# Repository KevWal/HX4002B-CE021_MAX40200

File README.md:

# HX4002B-CE021_MAX40200
PCB for a HX4002B 3.3v boost converter and 3 x MAX40200 ideal diodes.  

Ordered from https://JLCPCB.com/, looks and works great.

Allows this setup:
https://www.qsl.net/zl1rs/balloon6.html

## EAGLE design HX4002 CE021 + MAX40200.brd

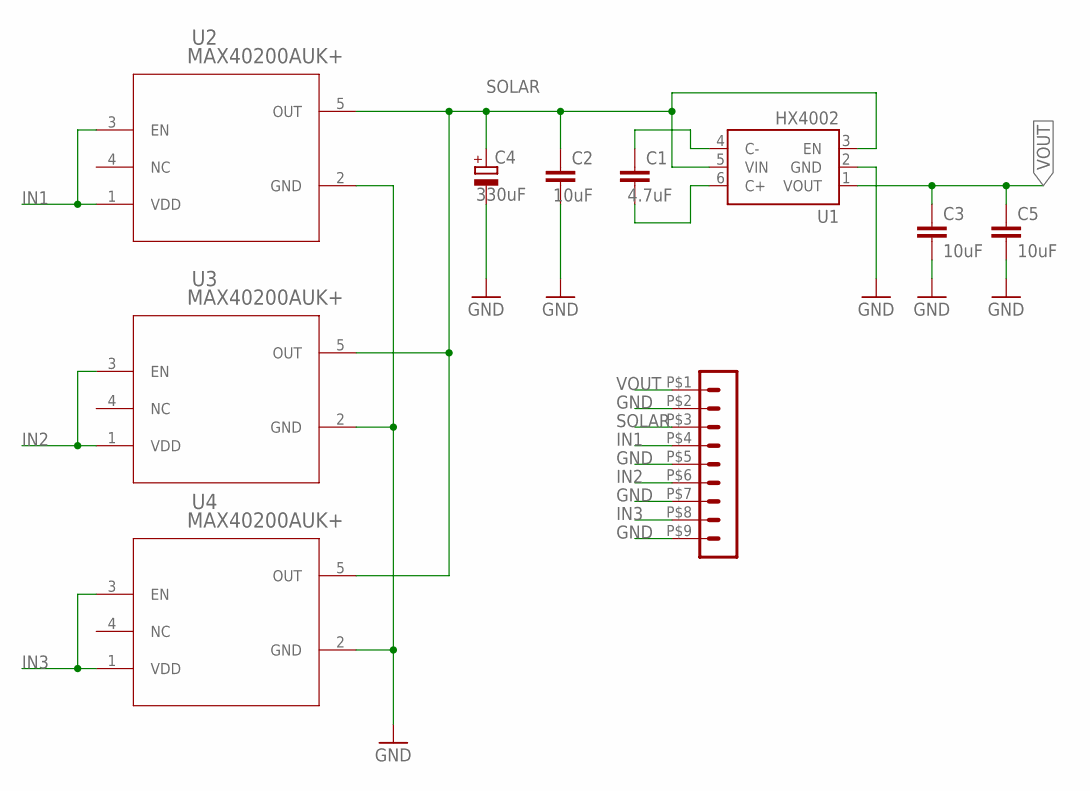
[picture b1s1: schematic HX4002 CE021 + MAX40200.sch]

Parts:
C1: 4.7uF; 0805
C2, C3, C5: 10uF; 0805
C4: 330uF; SMC_C
U1: HX4002; SOT23-6
U2, U3, U4: MAX40200AUK+; 21-0057F_MXM
X2: M_1R09_50MIL-V

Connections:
GND: C2.2, C3.2, C4.-, C5.2, U1.2 (GND), U2.2 (GND), U3.2 (GND), U4.2 (GND), X2.P$2 (2), X2.P$5 (5), X2.P$7 (7), X2.P$9 (9)
IN1: U2.1 (VDD), U2.3 (EN), X2.P$4 (4)
IN2: U3.1 (VDD), U3.3 (EN), X2.P$6 (6)
IN3: U4.1 (VDD), U4.3 (EN), X2.P$8 (8)
unnamed: C1.1, U1.4 (C-)
unnamed: C1.2, U1.6 (C+)
SOLAR: C2.1, C4.+, U1.3 (EN), U1.5 (VIN), U2.5 (OUT), U3.5 (OUT), U4.5 (OUT), X2.P$3 (3)
VOUT: C3.1, C5.1, U1.1 (VOUT), X2.P$1 (1)

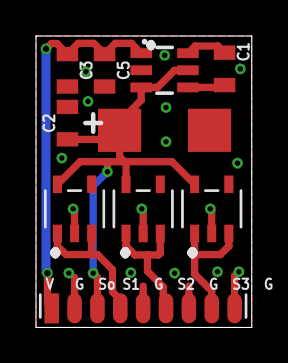
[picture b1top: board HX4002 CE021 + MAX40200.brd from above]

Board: 2 copper layers, 12.0 x 16.2 mm, 10 parts (0 on the bottom side), 8 nets.

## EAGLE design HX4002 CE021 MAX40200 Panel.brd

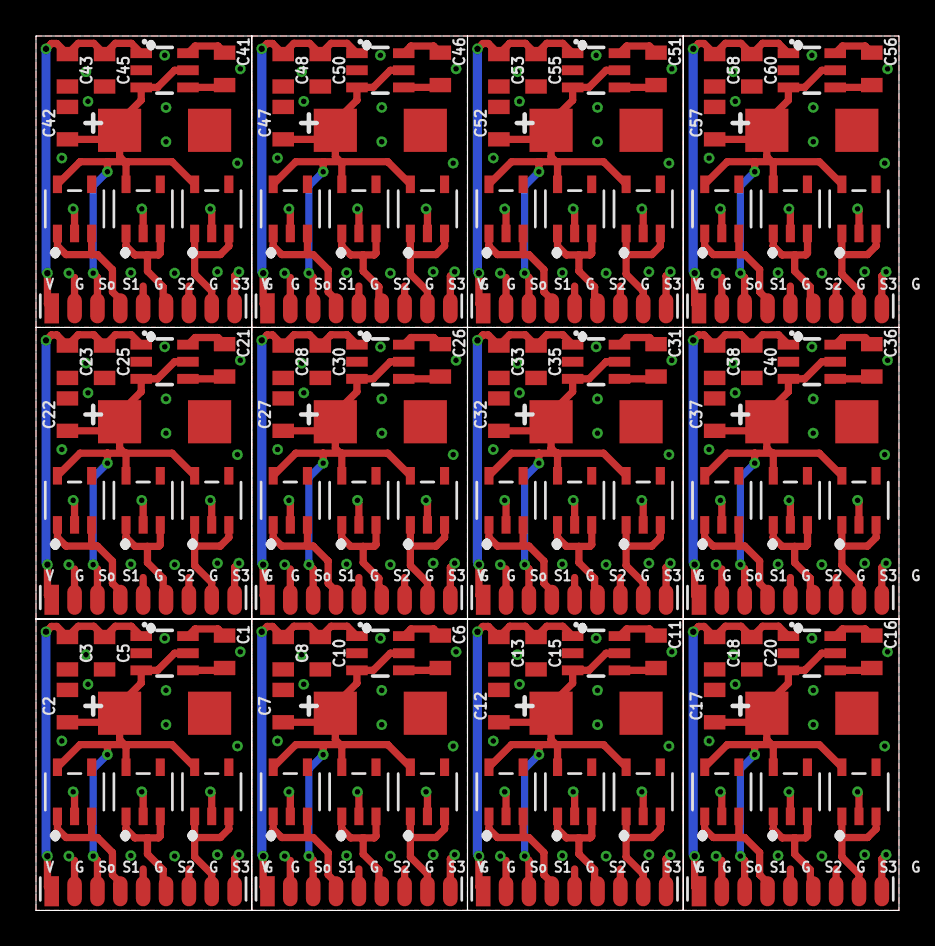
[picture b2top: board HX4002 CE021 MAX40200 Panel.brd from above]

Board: 2 copper layers, 47.9 x 48.6 mm, 120 parts (0 on the bottom side), 96 nets.

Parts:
C1, C6, C11, C16, C21, C26, C31, C36, C41, C46, C51, C56: 4.7uF; 0805
C2, C3, C5, C7, C8, C10, C12, C13, C15, C17, C18, C20, C22, C23, C25, C27, C28, C30, C32, C33, C35, C37, C38, C40, C42, C43, C45, C47, C48, C50, C52, C53, C55, C57, C58, C60: 10uF; 0805
C4, C9, C14, C19, C24, C29, C34, C39, C44, C49, C54, C59: 330uF; SMC_C
U1, U5, U9, U13, U17, U21, U25, U29, U33, U37, U41, U45: HX4002; SOT23-6
U2, U3, U4, U6, U7, U8, U10, U11, U12, U14, U15, U16, U18, U19, U20, U22, U23, U24, U26, U27, U28, U30, U31, U32, U34, U35, U36, U38, U39, U40, U42, U43, U44, U46, U47, U48: MAX40200AUK+; 21-0057F_MXM
X1, X2, X3, X4, X5, X6, X7, X8, X9, X10, X11, X12: M_1R09_50MIL-V

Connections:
GND: C2.2, C3.2, C4.-, C5.2, U1.2, U2.2, U3.2, U4.2, X2.P$2, X2.P$5, X2.P$7, X2.P$9
GND1: C7.2, C8.2, C9.-, C10.2, U5.2, U6.2, U7.2, U8.2, X1.P$2, X1.P$5, X1.P$7, X1.P$9
GND2: C12.2, C13.2, C14.-, C15.2, U9.2, U10.2, U11.2, U12.2, X3.P$2, X3.P$5, X3.P$7, X3.P$9
GND3: C17.2, C18.2, C19.-, C20.2, U13.2, U14.2, U15.2, U16.2, X4.P$2, X4.P$5, X4.P$7, X4.P$9
GND4: C22.2, C23.2, C24.-, C25.2, U17.2, U18.2, U19.2, U20.2, X5.P$2, X5.P$5, X5.P$7, X5.P$9
GND5: C27.2, C28.2, C29.-, C30.2, U21.2, U22.2, U23.2, U24.2, X6.P$2, X6.P$5, X6.P$7, X6.P$9
GND6: C32.2, C33.2, C34.-, C35.2, U25.2, U26.2, U27.2, U28.2, X7.P$2, X7.P$5, X7.P$7, X7.P$9
GND7: C37.2, C38.2, C39.-, C40.2, U29.2, U30.2, U31.2, U32.2, X8.P$2, X8.P$5, X8.P$7, X8.P$9
GND8: C42.2, C43.2, C44.-, C45.2, U33.2, U34.2, U35.2, U36.2, X9.P$2, X9.P$5, X9.P$7, X9.P$9
GND9: C47.2, C48.2, C49.-, C50.2, U37.2, U38.2, U39.2, U40.2, X10.P$2, X10.P$5, X10.P$7, X10.P$9
GND10: C52.2, C53.2, C54.-, C55.2, U41.2, U42.2, U43.2, U44.2, X11.P$2, X11.P$5, X11.P$7, X11.P$9
GND11: C57.2, C58.2, C59.-, C60.2, U45.2, U46.2, U47.2, U48.2, X12.P$2, X12.P$5, X12.P$7, X12.P$9
IN1: U2.1, U2.3, X2.P$4
IN2: U3.1, U3.3, X2.P$6
IN3: U4.1, U4.3, X2.P$8
IN4: U6.1, U6.3, X1.P$4
IN5: U7.1, U7.3, X1.P$6
IN6: U8.1, U8.3, X1.P$8
IN7: U10.1, U10.3, X3.P$4
IN8: U11.1, U11.3, X3.P$6
IN9: U12.1, U12.3, X3.P$8
IN10: U14.1, U14.3, X4.P$4
IN11: U15.1, U15.3, X4.P$6
IN12: U16.1, U16.3, X4.P$8
IN13: U18.1, U18.3, X5.P$4
IN14: U19.1, U19.3, X5.P$6
IN15: U20.1, U20.3, X5.P$8
IN16: U22.1, U22.3, X6.P$4
IN17: U23.1, U23.3, X6.P$6
IN18: U24.1, U24.3, X6.P$8
IN19: U26.1, U26.3, X7.P$4
IN20: U27.1, U27.3, X7.P$6
IN21: U28.1, U28.3, X7.P$8
IN22: U30.1, U30.3, X8.P$4
IN23: U31.1, U31.3, X8.P$6
IN24: U32.1, U32.3, X8.P$8
IN25: U34.1, U34.3, X9.P$4
IN26: U35.1, U35.3, X9.P$6
IN27: U36.1, U36.3, X9.P$8
IN28: U38.1, U38.3, X10.P$4
IN29: U39.1, U39.3, X10.P$6
IN30: U40.1, U40.3, X10.P$8
IN31: U42.1, U42.3, X11.P$4
IN32: U43.1, U43.3, X11.P$6
IN33: U44.1, U44.3, X11.P$8
IN34: U46.1, U46.3, X12.P$4
IN35: U47.1, U47.3, X12.P$6
IN36: U48.1, U48.3, X12.P$8
unnamed: C1.1, U1.4
unnamed: C6.1, U5.4
unnamed: C1.2, U1.6
unnamed: C6.2, U5.6
unnamed: C11.1, U9.4
unnamed: C11.2, U9.6
unnamed: C16.1, U13.4
unnamed: C16.2, U13.6
unnamed: C21.1, U17.4
unnamed: C21.2, U17.6
unnamed: C26.1, U21.4
unnamed: C26.2, U21.6
unnamed: C31.1, U25.4
unnamed: C31.2, U25.6
unnamed: C36.1, U29.4
unnamed: C36.2, U29.6
unnamed: C41.1, U33.4
unnamed: C41.2, U33.6
unnamed: C46.1, U37.4
unnamed: C46.2, U37.6
unnamed: C51.1, U41.4
unnamed: C51.2, U41.6
unnamed: C56.1, U45.4
unnamed: C56.2, U45.6
SOLAR: C2.1, C4.+, U1.3, U1.5, U2.5, U3.5, U4.5, X2.P$3
SOLAR1: C7.1, C9.+, U5.3, U5.5, U6.5, U7.5, U8.5, X1.P$3
SOLAR2: C12.1, C14.+, U9.3, U9.5, U10.5, U11.5, U12.5, X3.P$3
SOLAR3: C17.1, C19.+, U13.3, U13.5, U14.5, U15.5, U16.5, X4.P$3
SOLAR4: C22.1, C24.+, U17.3, U17.5, U18.5, U19.5, U20.5, X5.P$3
SOLAR5: C27.1, C29.+, U21.3, U21.5, U22.5, U23.5, U24.5, X6.P$3
SOLAR6: C32.1, C34.+, U25.3, U25.5, U26.5, U27.5, U28.5, X7.P$3
SOLAR7: C37.1, C39.+, U29.3, U29.5, U30.5, U31.5, U32.5, X8.P$3
SOLAR8: C42.1, C44.+, U33.3, U33.5, U34.5, U35.5, U36.5, X9.P$3
SOLAR9: C47.1, C49.+, U37.3, U37.5, U38.5, U39.5, U40.5, X10.P$3
SOLAR10: C52.1, C54.+, U41.3, U41.5, U42.5, U43.5, U44.5, X11.P$3
SOLAR11: C57.1, C59.+, U45.3, U45.5, U46.5, U47.5, U48.5, X12.P$3
VOUT: C3.1, C5.1, U1.1, X2.P$1
VOUT1: C8.1, C10.1, U5.1, X1.P$1
VOUT2: C13.1, C15.1, U9.1, X3.P$1
VOUT3: C18.1, C20.1, U13.1, X4.P$1
VOUT4: C23.1, C25.1, U17.1, X5.P$1
VOUT5: C28.1, C30.1, U21.1, X6.P$1
VOUT6: C33.1, C35.1, U25.1, X7.P$1
VOUT7: C38.1, C40.1, U29.1, X8.P$1
VOUT8: C43.1, C45.1, U33.1, X9.P$1
VOUT9: C48.1, C50.1, U37.1, X10.P$1
VOUT10: C53.1, C55.1, U41.1, X11.P$1
VOUT11: C58.1, C60.1, U45.1, X12.P$1

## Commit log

2020-10-24 Add files via upload
    As ordered from jlcpcb.com

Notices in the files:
parts and their libraries:
SparkFun-Capacitors: Licensing: Creative Commons ShareAlike 4.0 International - https://creativecommons.org/licenses/by-sa/4.0
COPYRIGHT: Copyright (C) 2018 Accelerated Designs. All rights reserved
